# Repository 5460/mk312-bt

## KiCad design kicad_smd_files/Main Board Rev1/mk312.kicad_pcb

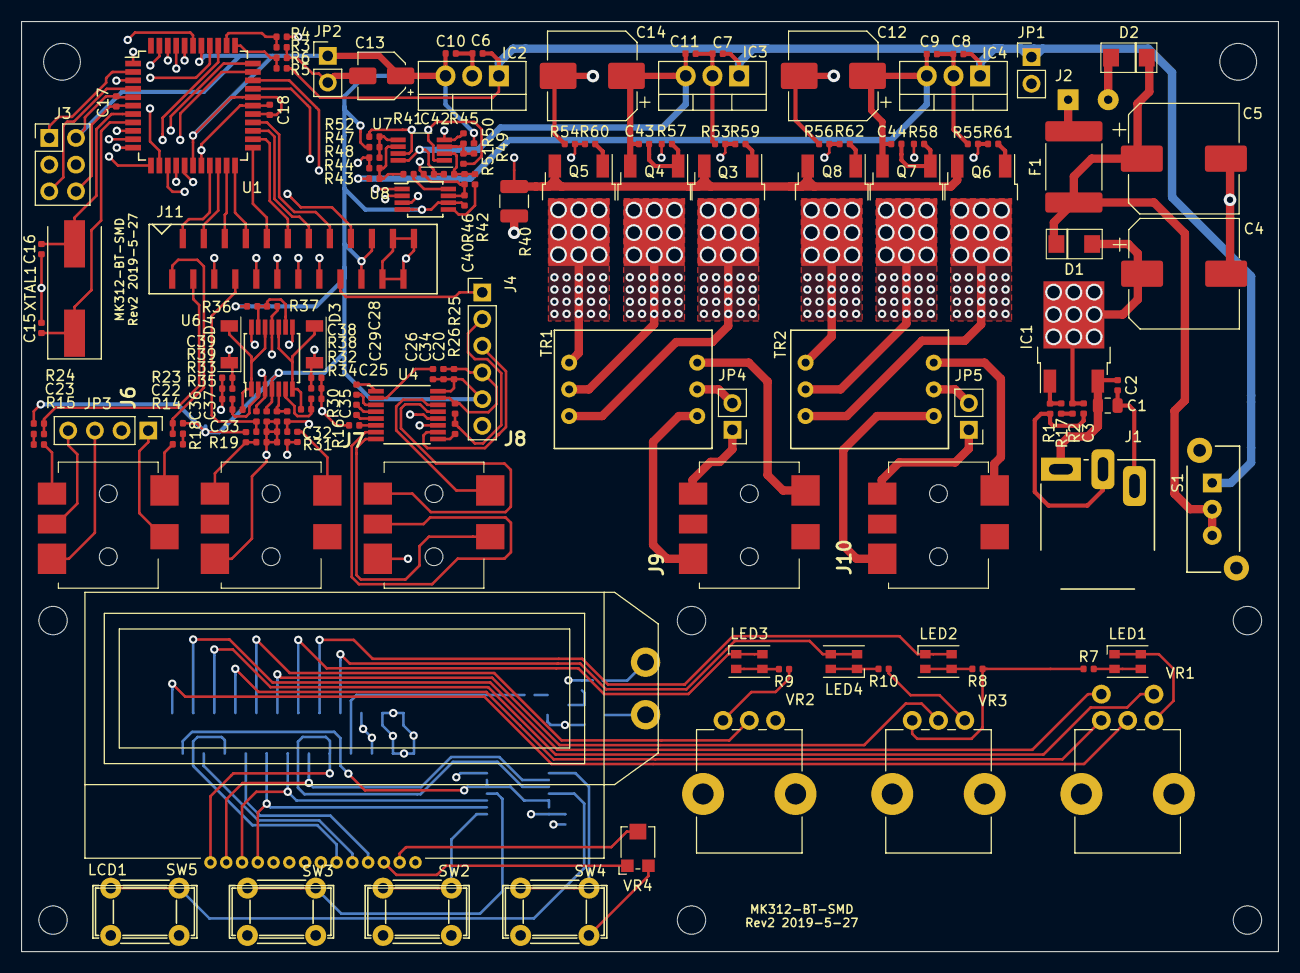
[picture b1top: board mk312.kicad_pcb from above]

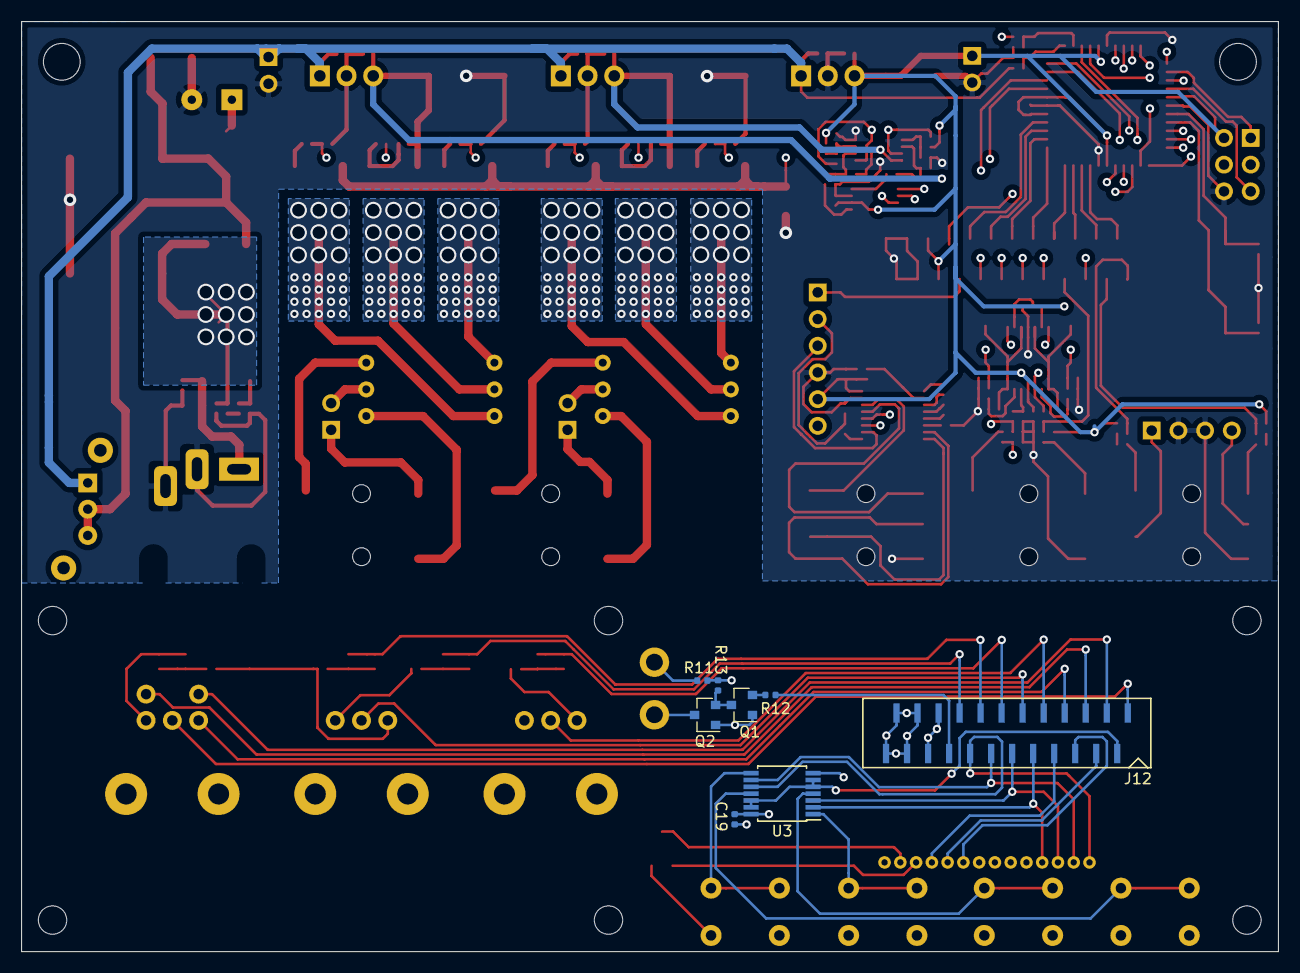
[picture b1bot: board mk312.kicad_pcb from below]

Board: 4 copper layers, 119.6 x 88.5 mm, 158 parts (8 on the bottom side), 138 nets.

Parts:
C1: 10uF; C_0805_2012Metric
C2, C3, C6, C7, C8, C9, C10, C11, C17, C18, C19, C20, C34, C35, C36, C37, C40, C42, C43, C44: 0.1uF; C_0402_1005Metric
C4, C5: 1000uF; CP_Elec_10x10
C12, C14: 470uF; CP_Elec_8x10
C13: 10uF; CP_Elec_4x5.4
C15, C16: 18pF; C_0402_1005Metric
C22, C23, C25, C26, C28, C29, C38, C39: 1uF; C_0402_1005Metric
C32, C33: 1nF; C_0402_1005Metric
D1, D2: 583-FM4004W-W; DO-214AC
D3, D4: LL4148; LL4148_SOD_80
F1: 1A Polyfuse; Fuse_2920_7451Metric
H1, H2, H3, H4, H5, H6: MountingHole; MountingHole_2.7mm_M2.5
H7, H8: MountingHole; MountingHole_3.5mm
IC1: LD1086BDTTR; TO-252-2
IC2: L7805CV; TO-220-3_Vertical
IC3, IC4: L7809ABV; TO-220-3_Vertical
J1: Barrel_Jack_MountingPin; DJ_Jack_PJ-003A
J2: +12V Battery; SolderWirePad_1x02_P3.81mm_Drill0.8mm
J3: Conn_02x03_Odd_Even; PinHeader_2x03_P2.54mm_Vertical
J4: RADIO INTERFACE; PinHeader_1x06_P2.54mm_Vertical
J6: LINE INPUT; SJ13515SMTTR
J7: REMOTE INPUT; SJ13515SMTTR
J8: LINK INPUT; SJ13515SMTTR
J9: OUTPUT A; SJ13515SMTTR
J10: OUTPUT B; SJ13515SMTTR
J11, J12: Conn_01x24_Male; HFW24S-2STE1LF
JP1: +12V; PinHeader_1x02_P2.54mm_Vertical
JP2: +5V; PinHeader_1x02_P2.54mm_Vertical
JP3: AUX LINE IN; PinHeader_1x04_P2.54mm_Vertical
JP4: A RING; PinHeader_1x02_P2.54mm_Vertical
JP5: B RING; PinHeader_1x02_P2.54mm_Vertical
LCD1: NHD-C0216AZ-FSW-GBW
LED1: POWER; LED_Cree-PLCC4_3.2x2.8mm_CCW
LED2: OUTPUT B; LED_Cree-PLCC4_3.2x2.8mm_CCW
LED3: OUTPUT A; LED_Cree-PLCC4_3.2x2.8mm_CCW
LED4: STATE; LED_Cree-PLCC4_3.2x2.8mm_CCW
Q1, Q2: MMBT3904; SOT-23
Q3, Q5, Q6, Q8: FQD13N10LTM; TO-252-2
Q4, Q7: FQD17P06TM; TO-252-2
R1, R30, R31, R34, R35, R38, R39, R53, R54, R55, R56: 100K; R_0402_1005Metric
R2, R3, R5, R25, R41, R42, R43, R44, R45, R46, R47, R49, R51, R52, R57, R58, R59, R60, R61, R62: 10K; R_0402_1005Metric
R4, R32, R33, R37: 2K; R_0402_1005Metric
R6: 3.3K; R_0402_1005Metric
R7, R8, R9, R10: 390; R_0402_1005Metric
R11: 47; R_0402_1005Metric
R12, R13, R18: 1.5K; R_0402_1005Metric
R14, R15, R16, R17, R19: 1K; R_0402_1005Metric
R23, R24, R36, R48, R50: 20K; R_0402_1005Metric
R26: 4.7K; R_0402_1005Metric
R40: 0.5R 1/2W; R_1210_3225Metric
S1: POWER; SW_E-Switch-LC-1258
SW2: LEFT/DOWN; E-Switch_Tactile_TL1105
SW3: OK; E-Switch_Tactile_TL1105
SW4: RIGHT/UP; E-Switch_Tactile_TL1105
SW5: MENU; E-Switch_Tactile_TL1105
TR1, TR2: 42TL004; 42TL
U1: ATmega16-16AU; TQFP-44_10x10mm_P0.8mm
U3: CD4066B; TSSOP-14_4.4x5mm_P0.65mm
U4: MAX202; TSSOP-16_4.4x5mm_P0.65mm
U6: LM324N; TSSOP-14_4.4x5mm_P0.65mm
U7: LM358N; VSSOP-8_3.0x3.0mm_P0.65mm
U8: LTC1661; MSOP-8_3x3mm_P0.65mm
VR1: MULTI-ADJ; Potentiometer_Alps_RK09K_Dual_Vertical
VR2: LEVEL A; Potentiometer_Alps_RK09K_Single_Vertical
VR3: LEVEL B; Potentiometer_Alps_RK09K_Single_Vertical
VR4: LCD CONTRAST; Potentiometer_Bourns_TC33X_Vertical
XTAL1: 8.0 MHz; Crystal_SMD_HC49-SD

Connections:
+5V: C10.1, C13.1, C17.1, C18.1, C20.1, C26.1, C34.2, C37.2, C40.1, IC2.3, J3.2, J4.5, J11.19, J11.20, JP2.1, R18.2, R23.1, R24.2, R36.2, R47.1, R49.1, U1.5, U1.17, U1.27, U1.29, U1.38, U4.16, U6.4, U8.4, U8.6
+5VD: C19.1, J12.19, J12.20, LCD1.3, R7.1, R8.1, R9.1, R11.1, R13.2, U3.14, VR2.3, VR3.3, VR4.1
+9V1: C11.1, C14.1, C42.1, C43.2, IC3.3, Q4.3, R45.1, U7.8
+9V2: C9.1, C12.1, C44.2, IC4.3, Q7.3, R43.1
+12V: C6.1, C7.1, C8.1, IC2.1, IC3.1, IC4.1, JP1.1, R5.2, S1.1
+VDC: C1.1, C2.1, IC1.3, J1.1, R3.1
GND: C1.2, C2.2, C3.2, C4.2, C5.2, C6.2, C7.2, C8.2, C9.2, C10.2, C11.2, C12.2, C13.2, C14.2, C15.2, C16.2, C17.2, C18.2, C20.2, C25.1, C32.2, C33.2, C34.1, C37.1, C38.2, C39.2, C40.2, C42.2, D2.2, IC2.2, IC3.2, IC4.2, J1.2, J1.3, J2.2, J3.6, J4.4, J6.S, J7.S, J8.S, J11.21, J11.22, J11.23, J11.24, JP1.2, JP2.2, JP3.2, JP3.3, R1.2, R4.2, R6.2, R19.1, R25.2, R30.2, R31.2, R32.2, R33.2, R37.1, R38.1, R39.1, R40.2, R44.2, R46.2, R48.2, R50.2, R53.2, R54.2, R55.2, R56.2, U1.6, U1.18, U1.28, U1.39, U4.15, U6.11, U7.4, U8.7
GNDD: C19.2, J12.21, J12.22, J12.23, J12.24, LCD1.1, LED1.1, Q1.1, Q2.1, R10.1, SW2.2, SW3.2, SW4.2, SW5.2, U3.7, VR1.1, VR2.1, VR3.1, VR4.3
unnamed: C3.1, C4.1, D1.2, IC1.2, R2.2
unnamed: C5.1, D1.1, D2.1, F1.1, S1.2, S1.3
unnamed: C15.1, U1.8, XTAL1.1
unnamed: C16.1, U1.7, XTAL1.2
unnamed: C22.1, R14.1
unnamed: C23.1, R15.1
unnamed: C25.2, U4.6
unnamed: C26.2, U4.2
unnamed: C28.1, U4.1
unnamed: C28.2, U4.3
unnamed: C29.1, U4.4
unnamed: C29.2, U4.5
unnamed: C35.2, R30.1, U6.5
unnamed: C36.2, R16.1, R31.1, U6.3
unnamed: C43.1, Q4.1, R57.1
unnamed: C44.1, Q7.1, R58.1
unnamed: D3.2, R34.1, U6.7, U6.10
unnamed: D4.2, R35.1, U6.1, U6.12
unnamed: F1.2, J2.1
unnamed: IC1.1, R1.1, R17.2
unnamed: J4.2, R25.1, R26.2
unnamed: J4.3, U4.10
unnamed: J6.R, R15.2
unnamed: J6.RN, JP3.4
unnamed: J6.T, R14.2
unnamed: J6.TN, JP3.1
unnamed: J7.R, R18.1, R19.2
unnamed: J7.T, R16.2
unnamed: J8.R, U4.13
unnamed: J8.RN, U4.7
unnamed: J8.T, U4.14
unnamed: J8.TN, U4.8
unnamed: J9.R, JP4.1
unnamed: J9.S, TR1.1
unnamed: J9.T, TR1.3
unnamed: J10.R, JP5.1
unnamed: J10.S, TR2.1
unnamed: J10.T, TR2.3
unnamed: JP4.2, TR1.2
unnamed: JP5.2, TR2.2
unnamed: LCD1.2, VR4.2
unnamed: LCD1.A, R11.2
unnamed: LCD1.K, Q2.3
unnamed: LED1.2, R7.2
unnamed: LED2.2, R8.2
unnamed: LED3.2, R9.2
unnamed: LED4.1, R10.2
unnamed: Q1.2, R12.2
unnamed: Q1.3, Q2.2, R13.1
unnamed: Q3.1, R59.1
unnamed: Q3.2, TR1.6
unnamed: Q4.2, TR1.5
unnamed: Q5.1, R60.1
unnamed: Q5.2, TR1.4
unnamed: Q6.1, R61.1
unnamed: Q6.2, TR2.6
unnamed: Q7.2, TR2.5
unnamed: Q8.1, R62.1
unnamed: Q8.2, TR2.4
unnamed: R3.2, R4.1, U1.35
unnamed: R5.1, R6.1, U1.34
unnamed: R2.1, R17.1
unnamed: R26.1, U4.9
unnamed: R32.1, R34.2, U6.6
unnamed: R33.1, R35.2, U6.2
unnamed: R36.1, R37.2, U6.9, U6.13
unnamed: R41.1, R43.2, R44.1, U7.6
unnamed: R41.2, U8.8
unnamed: R42.1, R45.2, R46.1, U7.2
unnamed: R42.2, U8.5
unnamed: R47.2, R48.1, R52.2, U7.5
unnamed: R49.2, R50.1, R51.2, U7.3
unnamed: R51.1, R57.2, U7.1
unnamed: R52.1, R58.2, U7.7
unnamed: SW2.1, U3.1
unnamed: SW3.1, U3.4
unnamed: SW4.1, U3.8
unnamed: SW5.1, U3.11
PA0: Q3.3, Q5.3, Q6.3, Q8.3, R40.1, U1.37
PA1: C32.1, C35.1, J11.5, U1.36
PA1-PANEL: J12.5, VR1.2
PA4: J11.9, U1.33
PA4-PANEL: J12.9, VR2.2
PA5: J11.11, U1.32
PA5-PANEL: J12.11, VR3.2
PA6: C39.1, D4.1, R39.2, U1.31
PA7: C38.1, D3.1, R38.2, U1.30
PB0: R55.1, R61.2, U1.40
PB1: R56.1, R62.2, U1.41
PB2: R53.1, R59.2, U1.42
PB3: R54.1, R60.2, U1.43
PB5: J3.4, U1.1, U8.3
PB6: J3.1, U1.2
PB7: J3.3, U1.3, U8.2
PC0: J11.2, U1.19
PC0-PANEL: J12.2, U3.5, U3.6, U3.12, U3.13
PC1: J11.4, U1.20
PC1-PANEL: J12.4, LCD1.5
PC2: J11.6, U1.21
PC2-PANEL: J12.6, LCD1.6
PC3: J11.8, U1.22
PC3-PANEL: J12.8, LCD1.4
PC4: J11.10, U1.23
PC4-PANEL: J12.10, LCD1.11, U3.2
PC5: J11.12, U1.24
PC5-PANEL: J12.12, LCD1.12, U3.3
PC6: J11.14, U1.25
PC6-PANEL: J12.14, LCD1.13, U3.9
PC7: J11.16, U1.26
PC7-PANEL: J12.16, LCD1.14, U3.10
PD0: U1.9, U4.12
PD1: U1.10, U4.11
PD2: U1.11, U6.14
PD3: U1.12, U6.8
PD5: J11.15, U1.14
PD5-PANEL: J12.15, LED2.1
PD6: J11.13, U1.15
PD6-PANEL: J12.13, LED3.1
PD7: J11.18, U1.16
PD7-PANEL: J12.18, R12.1
RB4: C33.1, C36.1, J11.7
RB4-PANEL: J12.7, VR1.4
RB9: C23.2, J11.3, R24.1
RB9-PANEL: J12.3, VR1.5
RB10: C22.2, J11.1, R23.2
RB10-PANEL: J12.1, VR1.3
STATE: J4.1, J11.17
STATE-PANEL: J12.17, LED4.2
~CS: U1.13, U8.1
~RESET: J3.5, U1.4

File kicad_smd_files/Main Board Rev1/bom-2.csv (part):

"Item","Qty","Reference(s)","Value","LibPart","Footprint","Datasheet","Allied Price/Stock","Allied_Number","Description","Height","Manufacturer_Name","Manufacturer_Part_Number","Mouser Part Number","Mouser Price/Stock","Notes","RS Part Number","RS Price/Stock"
"1","1","C1","10uF","Device:C_Small","Capacitor_SMD:C_0805_2012Metric","https://www.mouser.com/datasheet/2/315/ABA0000C1181-947564.pdf","","","","","Taiyo Yuden","TMK212BBJ106MG-T","963-TMK212BBJ106MG-T","","","",""
"2","20","C2, C3, C6, C7, C8, C9, C10, C11, C17, C18, C19, C20, C34, C35, C36, C37, C40, C42, C43, C44","0.1uF","Device:C_Small","Capacitor_SMD:C_0402_1005Metric","https://www.mouser.com/datasheet/2/281/murata_03122018_GCM_S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","","","","","Yageo","CC0402KRX7R7BB104","603-CC402KRX7R7BB104","","","",""
"3","2","C4, C5","1000uF","Device:CP1","Capacitor_SMD:C_Elec_10x10.2","https://www.mouser.com/datasheet/2/315/ABA0000C1240-1130326.pdf","","","","","Panasonic","EEE-FK1C102SP","667-EEE-FK1C102SP","","","",""
"4","2","C12, C14","470uF","Device:CP1","Capacitor_SMD:C_Elec_8x10.2","https://www.mouser.com/datasheet/2/315/ABA0000C1181-947564.pdf","","","","","Panasonic","EEE-FK1C471P","667-EEE-FK1C471P","","","",""
"5","1","C13","10uF","Device:CP1","Capacitor_SMD:C_Elec_4x5.4","https://www.mouser.com/datasheet/2/315/ABA0000C1181-947564.pdf","","","","","Panasonic","EEE-1CA100SR","667-EEE-1CA100SR","","","",""
"6","2","C15, C16","18pF","Device:C_Small","Capacitor_SMD:C_0402_1005Metric","https://www.mouser.com/datasheet/2/281/GCM1555C1H180FA16-01-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","","","","","Yageo","CC0402JRNPO9BN180","603-CC402JRNPO9BN180","","","",""
"7","8","C22, C23, C25, C26, C28, C29, C38, C39","1uF","Device:C_Small","Capacitor_SMD:C_0402_1005Metric","https://www.mouser.com/datasheet/2/281/murata_03052018_GRM_S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","","","","","Taiyo Yuden","JMK105C6105MV-F","963-JMK105C6105MV-F","","","",""
"8","2","C32, C33","1nF","Device:C_Small","Capacitor_SMD:C_0402_1005Metric","https://www.mouser.com/datasheet/2/281/murata_03122018_GCM_S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","","","","","KEMET","C0402C102K5RAC7411","80-C0402C102K5R7411","","","",""
"9","2","D1, D2","583-FM4004W-W","Diode:1N4004","mk312-smd-footprints:DO-214AC","http://www.rectron.com/public/product_datasheets/fm4001w-fm4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","","","Rectifiers 1A, 400V","2.31","Rectron","583-FM4004W-W","583-FM4004W-W","https://www.mouser.com/Search/Refine.aspx?Keyword=583-FM4004W-W","","",""
"10","2","D3, D4","LL4148","Device:D","mk312-smd-footprints:LL4148_SOD_80","https://www.mouser.com/datasheet/2/427/1n4148w-240387.pdf","","","","","ON Semiconductor","LL4148","512-LL4148","","","",""
"11","1","F1","1A Polyfuse","Device:Polyfuse","Fuse:Fuse_2920_7451Metric","https://www.mouser.com/datasheet/2/643/0ZCF_Nov2016-1133542.pdf","","","","","Bel Fuse","0ZCF0100AF2A","530-0ZCF0100AF2A","","","",""
"12","6","H1, H2, H3, H4, H5, H6","MountingHole","Mechanical:MountingHole","MountingHole:MountingHole_2.7mm_M2.5","~","","","","","","","","","","",""
"13","2","H7, H8","MountingHole","Mechanical:MountingHole","MountingHole:MountingHole_3.5mm","~","","","","","","","","","","",""
"14","1","IC1","LD1086BDTTR","Regulator_Linear:NCP1117-ADJ_TO252","Package_TO_SOT_SMD:TO-252-2","https://www.mouser.com/datasheet/2/389/ld1086-974047.pdf","","","","","STMicroelectronics","LD1086BDTTR","511-LD1086BDTTR","","","",""
"15","1","IC2","L7805CV","Regulator_Linear:L7805","Package_TO_SOT_THT:TO-220-3_Vertical","https://www.mouser.com/datasheet/2/389/l78-974043.pdf","http://www.alliedelec.com/stmicroelectronics-l7805abd2t-tr/7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","70407657","","4.6","STMicroelectronics","L7805CV","511-L7805CV","https://www.mouser.com/Search/Refine.aspx?Keyword=511-L7805ABD2T-TR","","7931342P","http://uk.rs-online.com/web/p/products/7931342P"
"16","2","IC3, IC4","L7809ABV","Regulator_Linear:L7809","Package_TO_SOT_THT:TO-220-3_Vertical","https://www.mouser.com/datasheet/2/389/l78-974043.pdf","","","","","STMicroelectronics","L7809ABV","511-L7809ABV","https://www.mouser.com/Search/Refine.aspx?Keyword=511-L7809ABD2T-TR","","",""
"17","1","J1","Barrel_Jack_MountingPin","Connector:Barrel_Jack_Switch","mk312-smd-footprints:DJ_Jack_PJ-003A","https://www.mouser.com/datasheet/2/670/pj-002a-1312176.pdf","","","","","CUI","PJ-003A","490-PJ-003A","","","",""
"18","1","J2","+12V Battery","Connector_Generic:Conn_01x02","Connector_Wire:SolderWirePad_1x02_P3.81mm_Drill0.8mm","~","","","","","","","","","","",""
"19","1","J3","Conn_02x03_Odd_Even","Connector_Generic:Conn_02x03_Odd_Even","Connector_PinHeader_2.54mm:PinHeader_2x03_P2.54mm_Vertical","https://www.mouser.com/datasheet/2/418/NG_CD_103328_P5-1229876.pdf","","","","","TE Connectivity / AMP","4-103328-2","571-4-103328-2","","","",""
"20","1","J4","RADIO INTERFACE","Connector_Generic:Conn_01x06","Connector_PinHeader_2.54mm:PinHeader_1x06_P2.54mm_Vertical","https://www.mouser.com/datasheet/2/527/slw-1370256.pdf","","","","","Samtec","SLW-106-01-G-S","200-SLW10601GS","","","",""
"21","1","J6","LINE INPUT","Connector:AudioJack3_SwitchTR","mk312-smd-footprints:SJ13515SMTTR","https://www.mouser.com/datasheet/2/670/sj1-351x-smt_series-1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","","","","","CUI","SJ1-3515-SMT-TR","490-SJ1-3515-SMT-TR","","","",""
"22","1","J7","REMOTE INPUT","Connector:AudioJack3_SwitchTR","mk312-smd-footprints:SJ13515SMTTR","https://www.mouser.com/datasheet/2/670/sj1-351x-smt_series-1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","","","","","CUI","SJ1-3515-SMT-TR","490-SJ1-3515-SMT-TR","","","",""
"23","1","J8","LINK INPUT","Connector:AudioJack3_SwitchTR","mk312-smd-footprints:SJ13515SMTTR","https://www.mouser.com/datasheet/2/670/sj1-351x-smt_series-1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","","","","","CUI","SJ1-3515-SMT-TR","490-SJ1-3515-SMT-TR","","","",""
"24","1","J9","OUTPUT A","Connector:AudioJack3_SwitchTR","mk312-smd-footprints:SJ13515SMTTR","https://www.mouser.com/datasheet/2/670/sj1-351x-smt_series-1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","","","","","CUI","SJ1-3515-SMT-TR","490-SJ1-3515-SMT-TR","","","",""
"25","1","J10","OUTPUT B","Connector:AudioJack3_SwitchTR","mk312-smd-footprints:SJ13515SMTTR","https://www.mouser.com/datasheet/2/670/sj1-351x-smt_series-1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","","","","","CUI","SJ1-3515-SMT-TR","490-SJ1-3515-SMT-TR","","","",""
"26","1","J11","Conn_01x24_Male","Connector:Conn_01x24_Male","mk312-smd-footprints:HFW24S-2STE1LF","https://www.mouser.com/datasheet/2/18/hfw_s-2ste1lf-1365432.pdf","","","","","Amphenol FCI","HFW24S-2STE1LF","649-HFW24S-2STE1LF","","","",""
"27","1","J12","Conn_01x24_Male","mk312:Conn_01x24_Male_Power","mk312-smd-footprints:HFW24S-2STE1LF","https://www.mouser.com/datasheet/2/18/hfw_s-2ste1lf-1365432.pdf","","","","","Amphenol FCI","HFW24S-2STE1LF","649-HFW24S-2STE1LF","","","",""
"28","1","JP1","+12V","Connector_Generic:Conn_01x02","Connector_PinHeader_2.54mm:PinHeader_1x02_P2.54mm_Vertical","https://www.mouser.com/datasheet/2/418/NG_CD_146285_J-649398.pdf","","","","","TE Connectivity","5-146285-2","571-5-146285-2","","","",""
"29","1","JP2","+5V","Connector_Generic:Conn_01x02","Connector_PinHeader_2.54mm:PinHeader_1x02_P2.54mm_Vertical","https://www.mouser.com/datasheet/2/418/NG_CD_146285_J-649398.pdf","","","","","TE Connectivity","5-146285-2","571-5-146285-2","","","",""
"30","1","JP3","AUX LINE IN","Connector_Generic:Conn_01x04","Connector_PinHeader_2.54mm:PinHeader_1x04_P2.54mm_Vertical","https://www.mouser.com/datasheet/2/418/NG_CD_146285_J-649398.pdf","","","","","TE Connectivity","5-146285-2","571-5-146285-2","","","",""
"31","1","JP4","A RING","Connector_Generic:Conn_01x02","Connector_PinHeader_2.54mm:PinHeader_1x02_P2.54mm_Vertical","https://www.mouser.com/datasheet/2/418/NG_CD_146285_J-649398.pdf","","","","","TE Connectivity","5-146285-2","571-5-146285-2","","","",""
"32","1","JP5","B RING","Connector_Generic:Conn_01x02","Connector_PinHeader_2.54mm:PinHeader_1x02_P2.54mm_Vertical","https://www.mouser.com/datasheet/2/418/NG_CD_146285_J-649398.pdf","","","","","TE Connectivity","5-146285-2","571-5-146285-2","","","",""
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
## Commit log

2019-05-26 Smaller PCB, cheaper parts
2019-05-27 part footprint corrections
2019-05-27 New box
2019-05-27 Updated case design
2019-05-27 PCB svg
2020-02-23 Some tweaks and modifications
